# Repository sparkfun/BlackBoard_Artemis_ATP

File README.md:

**NOTE:** *This product has been retired from our catalog. There is an updated RedBoard version available: [DEV-15442]https://www.sparkfun.com/products/15442). If you are looking for more up-to-date info, please check out some of these resources to see how other users are still hacking and improving on this product version.*

* *[SparkFun Artemis Forum](https://forum.sparkfun.com/viewforum.php?f=167)*
* *[Comments Here on GitHub](https://github.com/sparkfun/BlackBoard_Artemis_ATP/issues)*

SparkFun BlackBoard Artemis ATP
============================

[*SparkFun BlackBoard Artemis ATP (SPX-15412)*](https://www.sparkfun.com/products/15412)

The BlackBoard Artemis ATP is affectionately called 'All the Pins!' at SparkFun. The Artemis module has 48 GPIO and this board breaks out absolutely every one of them in a familiar Mega like form factor. What's with the silkscreen labels? They're all over the place. We decided to label the pins as they are assigned on the Apollo3 IC itself. This makes finding the pin with the function you desire a lot easier. Have a look at the [full pin map](https://cdn.sparkfun.com/assets/8/2/3/3/c/Apollo3_Pad_Mapping.pdf) from the Apollo3 datasheet. If you really need to test out the 4-bit SPI functionality of the Artemis you're going to need to access pins 4, 22, 23, and 26. Need to try out the differential ADC port 1? Pins 14 and 15. The BlackBoard Artemis ATP will allow you to flex the impressive capabilities of the Artemis module.

The BlackBoard Artemis ATP has the improved power conditioning and USB to serial that we've refined over the years on our BlackBoard line of products. A modern USB-C connector make programming easy. A Qwiic connector makes I<sup>2</sup>C easy. The ATP is fully compatible with SparkFun's Arduino core and can be programmed easily under the Arduino IDE. We've exposed the JTAG connector for more advanced users who prefer to use the power and speed of professional tools. If you need a *lot* of a GPIO with a simple to program, ready to go to market module, the ATP is the fix you need. We've added a digital MEMS microphone for folks wanting to experiment with always-on voice commands with TensorFlow and machine learning. We've even added a convenient jumper to measure current consumption for low power testing.

With 1M flash and 384k RAM you'll have plenty of room for your sketches. The Artemis module runs at 48MHz with a 96MHz turbo mode available and with Bluetooth to boot!

The SparkFun BlackBoard Artemis ATP is a powerful platform if you're interesting in testing out the full capabilities of the SparkFun Artemis module. If you're looking for more compact solution, be sure to checkout our Nano and Uno footprints for more hacker friendly products.

**Note:** We are actively working on getting FCC and compliance certifications for the SparkFun Artemis Module. Once our certifications are complete we will be moving the ATP to a RedBoard format with the FCC Certified version of the Artemis on board. *Please be aware* that this could happen as soon as a few weeks to a month so this BlackBoard version is for those of you who can't wait and want to start using the SparkFun Artemis as soon as possible!

Repository Contents
-------------------
* **/Hardware** - Eagle design files (.brd, .sch)

Documentation
-------------------
* **[BlackBoard Artemis ATP Hookup Guide](https://learn.sparkfun.com/tutorials/hookup-guide-for-the-blackboard-artemis-atp)** - Hookup Guide for the BlackBoard Artemis ATP
* **[Designing with the SparkFun Artemis](https://learn.sparkfun.com/tutorials/designing-with-the-sparkfun-artemis)** - Layout and design considerations when using the Artemis module.
* **[Artemis Development with Arduino](https://learn.sparkfun.com/tutorials/artemis-development-with-arduino)** - Introduction to the Arduino core for the Artemis Module.
* **[Ambiq Apollo3 SDK SetUp](https://learn.sparkfun.com/tutorials/using-sparkfun-edge-board-with-ambiq-apollo3-sdk)** - Getting set up with the Apollo3 Software Development Kit.
* **[CH340E USB to serial IC Drivers](https://www.sparkfun.com/ch340)**

License Information
-------------------

This product is _**open source**_! 

Please review the LICENSE.md file for license information. 

If you have any questions or concerns on licensing, please contact techsupport@sparkfun.com.

Please use, reuse, and modify these files as you see fit. Please maintain attribution to SparkFun Electronics and release any derivative under the same license.

Distributed as-is; no warranty is given.

- Your friends at SparkFun.

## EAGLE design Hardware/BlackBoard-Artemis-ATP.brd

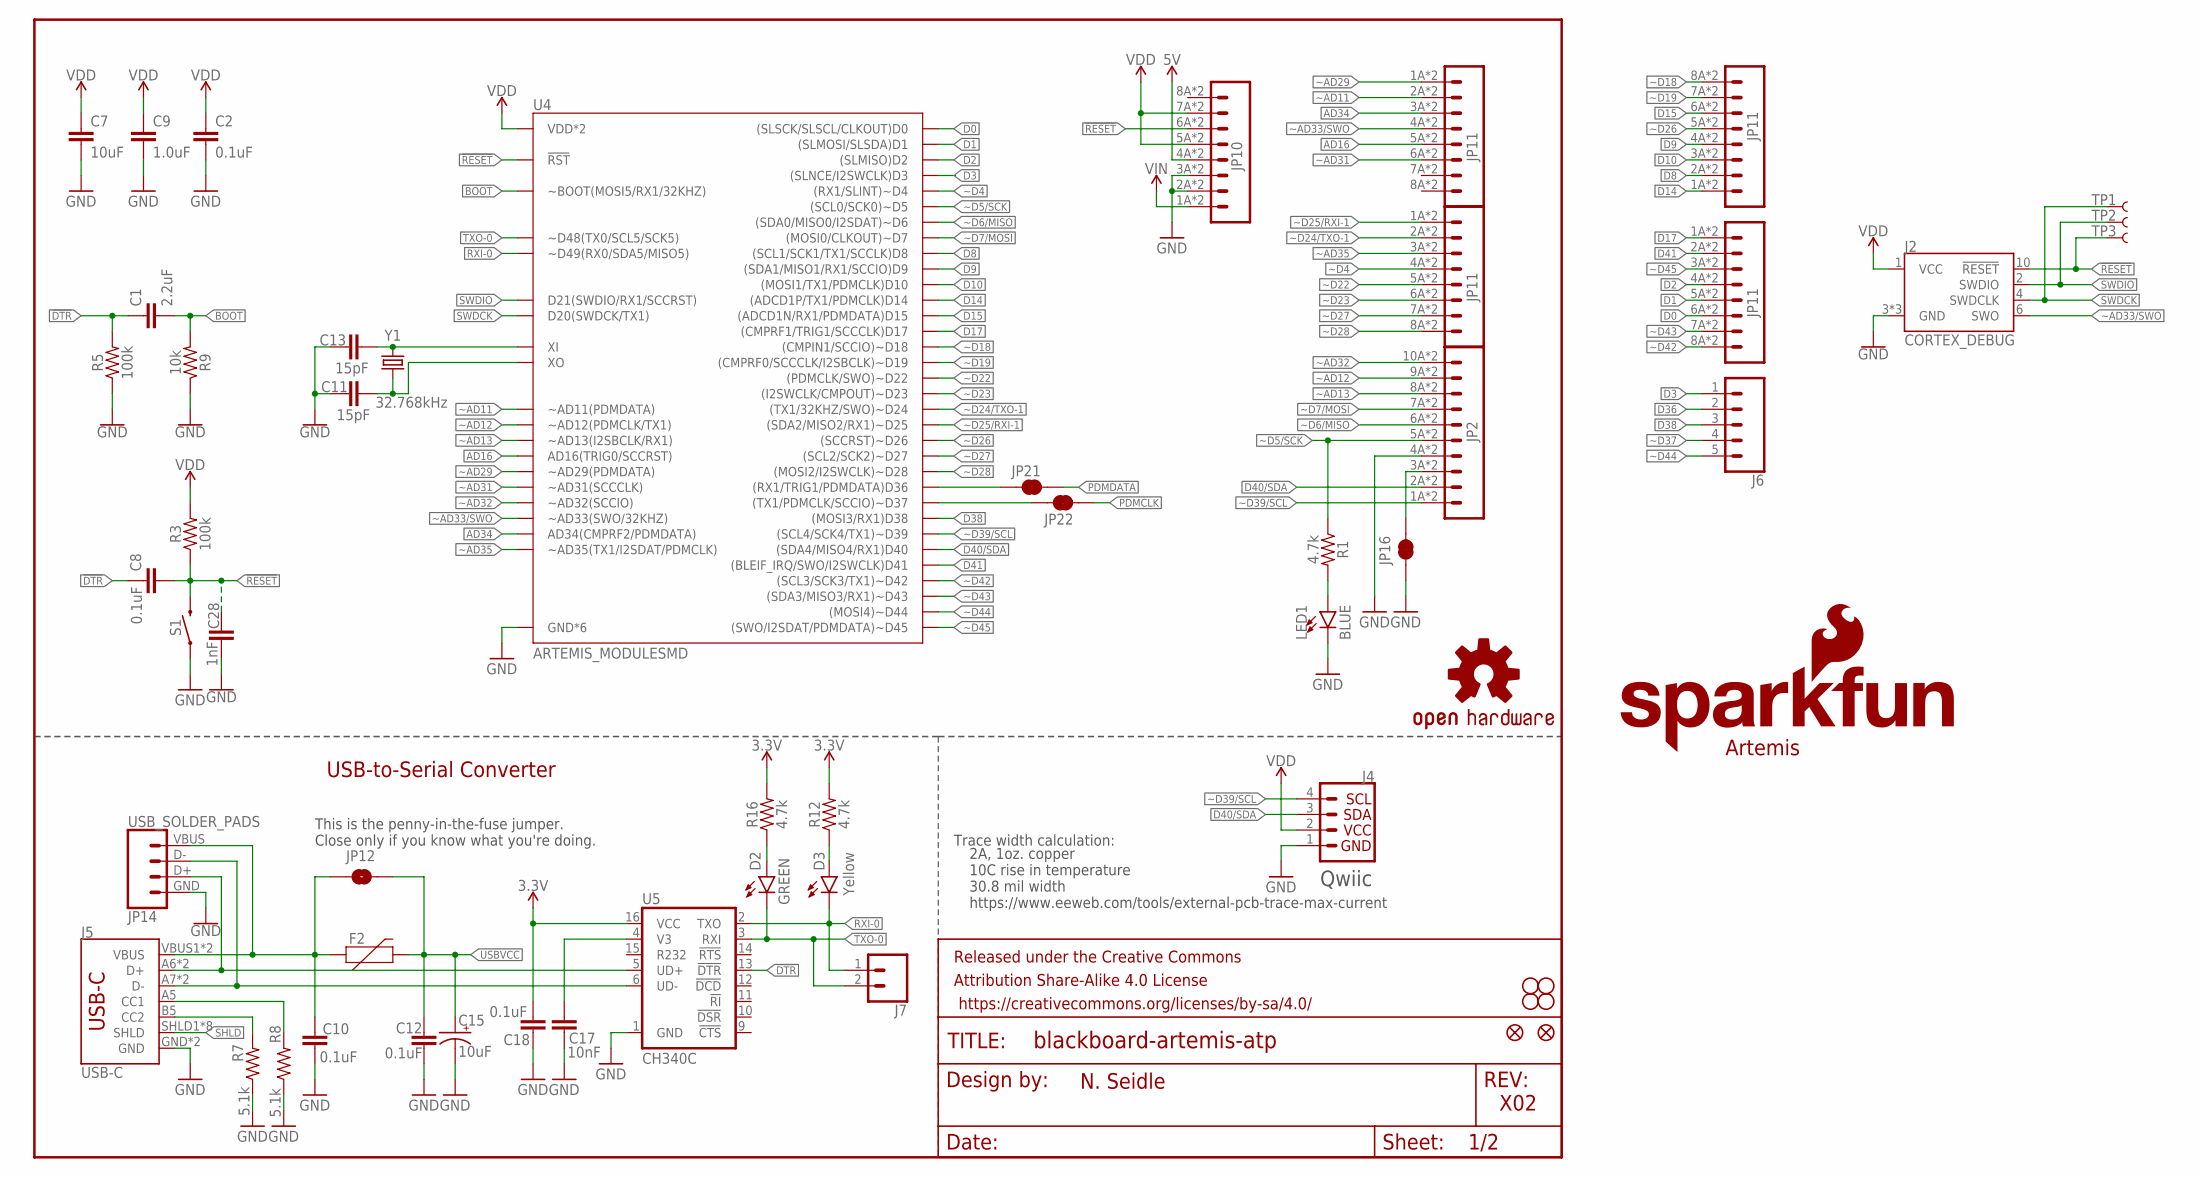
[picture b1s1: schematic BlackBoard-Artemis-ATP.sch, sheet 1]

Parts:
C1: 2.2uF; 0603
C2, C8, C10, C12, C18: 0.1uF; 0603
C7: 10uF; 0603
C9: 1.0uF; 0603
C11, C13: 15pF; 0603
C15: 10uF; EIA3216
C17: 10nF; 0603
C28: 1nF; 0603
D2: GREEN; LED-1206
D3: Yellow; LED-1206
F2: 6V/2A; 1210
FRAME1: FRAME-LETTER; CREATIVE_COMMONS
J2: CORTEX_DEBUG; 2X5-PTH-1.27MM-NO_SILK
J4: QWIIC_CONNECTORJS-1MM; JST04_1MM_RA
J5: USB-C; USB-C-16P
J6: CONN_05NO_SILK; 1X05_NO_SILK
J7: CONN_021X02_NO_SILK; 1X02_NO_SILK
JP1: SFE_LOGO_NAME.1_INCH; SFE_LOGO_NAME_.1
JP2: M10SMD_COMBO; 1X10_SMD_COMBINED
JP3, JP4, JP5, JP6: STAND-OFF
JP7: SFE_LOGO_FLAME.1_INCH; SFE_LOGO_FLAME_.1
JP8, JP9: FIDUCIAL1X2; FIDUCIAL-1X2
JP10: M08SMD-COMBO; 1X08_SMD_COMBINED
JP11, JP13, JP19, JP20: JP11; 1X08_SMD_COMBINED
JP12: JUMPER-SMT_2_NO_SILK; SMT-JUMPER_2_NO_SILK
JP14: USB_SOLDER_PADS; USB-SOLDER-PADS
JP16, JP21, JP22: JUMPER-SMT_2_NC_TRACE_SILK; SMT-JUMPER_2_NC_TRACE_SILK
LED1: BLUE; LED-1206
R1, R12, R16: 4.7k; 0603
R3, R5: 100k; 0603
R7, R8: 5.1k; 0603
R9: 10k; 0603
S1: MOMENTARY-SWITCH-SPST-SMD-5.2-TALL-REDUNDANT; TACTILE_SWITCH_SMD_5.2MM
TP1, TP2, TP3: TEST-POINT3X5; PAD.03X.05
U4: ARTEMIS_MODULESMD; ARTEMIS_FP
U5: CH340C; SO016
U$16: OSHW-LOGOS; OSHW-LOGO-S
Y1: 32.768kHz; CRYSTAL-SMD-3.2X1.5MM

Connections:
3.3V: C18.1, R12.2, R16.2, U5.16 (VCC); also elsewhere on the board
5V: JP10.4A (4), JP10.4B (4); also elsewhere on the board
!DTR: C1.1, C8.1, R5.2, U5.13 (!DTR)
!RESET: C8.2, C28.1, J2.10 (!RESET), JP10.6A (6), JP10.6B (6), R3.1, S1.3 (2), S1.4 (2), TP3.P$1, U4.~RST (!RST)
AD16: JP13.5A (5), JP13.5B (5), U4.AD16 (AD16(TRIG0/SCCRST))
AD34: JP13.3A (3), JP13.3B (3), U4.AD34 (AD34(CMPRF2/PDMDATA))
BOOT: C1.2, R9.2, U4.BOOT (~BOOT(MOSI5/RX1/32KHZ))
CC1: J5.A5 (CC1), R8.2
CC2: J5.B5 (CC2), R7.2
D0: JP20.6A (6), JP20.6B (6), U4.D0 ((SLSCK/SLSCL/CLKOUT)D0)
D1: JP20.5A (5), JP20.5B (5), U4.D1 ((SLMOSI/SLSDA)D1)
D2: JP20.4A (4), JP20.4B (4), U4.D2 ((SLMISO)D2)
D3: J6.1, U4.D3 ((SLNCE/I2SWCLK)D3)
D8: JP19.2A (2), JP19.2B (2), U4.D8 ((SCL1/SCK1/TX1/SCCLK)D8)
D9: JP19.4A (4), JP19.4B (4), U4.D9 ((SDA1/MISO1/RX1/SCCIO)D9)
D10: JP19.3A (3), JP19.3B (3), U4.D10 ((MOSI1/TX1/PDMCLK)D10)
D14: JP19.1A (1), JP19.1B (1), U4.D14 ((ADCD1P/TX1/PDMCLK)D14)
D15: JP19.6A (6), JP19.6B (6), U4.D15 ((ADCD1N/RX1/PDMDATA)D15)
D17: JP20.1A (1), JP20.1B (1), U4.D17 ((CMPRF1/TRIG1/SCCCLK)D17)
D36: J6.2, JP21.1, U4.D36 ((RX1/TRIG1/PDMDATA)D36)
D38: J6.3, U4.D38 ((MOSI3/RX1)D38)
D40/SDA: J4.3, JP2.2A (2), JP2.2B (2), U4.D40 ((SDA4/MISO4/RX1)D40)
D41: JP20.2A (2), JP20.2B (2), U4.D41 ((BLEIF_IRQ/SWO/I2SWCLK)D41)
D+: J5.A6 (D+), J5.B6 (D+), JP14.D+ (3), U5.5 (UD+)
D-: J5.A7 (D-), J5.B7 (D-), JP14.D- (2), U5.6 (UD-)
GND: C2.1, C7.2, C9.2, C10.2, C11.1, C12.2, C13.1, C15.-, C17.2, C18.2, C28.2, J2.3 (GND), J2.5 (GND), J2.9 (GND), J4.1, J5.GND, J5.GND2 (GND), JP2.4A (4), JP2.4B (4), JP10.2A (2), JP10.2B (2), JP10.3A (3), JP10.3B (3), JP14.GND (4), JP16.1, LED1.C, R5.1, R7.1, R8.1, R9.1, S1.1, S1.2 (1), U4.GND@1 (GND*6), U4.GND@22 (GND*6), U4.GND@38 (GND*6), U4.GND@39 (GND*6), U4.GND@47 (GND*6), U4.GND@59 (GND*6), U5.1 (GND); also elsewhere on the board
unnamed: LED1.A, R1.2
unnamed: D2.A, R16.1
unnamed: C17.1, U5.4 (V3)
unnamed: C11.2, U4.XO, Y1.P$2 (2)
unnamed: C13.2, U4.XI, Y1.P$1 (1)
unnamed: D3.A, R12.1
unnamed: JP2.3A (3), JP2.3B (3), JP16.2
PDMCLK: JP22.2; also elsewhere on the board
PDMDATA: JP21.2; also elsewhere on the board
RXI-0: D3.C, J7.1, U4.RXI-0 (~D49(RX0/SDA5/MISO5)), U5.2 (TXO)
SHLD: J5.SHLD1 (SHLD), J5.SHLD2 (SHLD), J5.SHLD3 (SHLD), J5.SHLD4 (SHLD), J5.SHLD5 (SHLD), J5.SHLD6 (SHLD), J5.SHLD7 (SHLD), J5.SHLD8 (SHLD)
SWDCK: J2.4 (SWDCLK), TP1.P$1, U4.SWDCK (D20(SWDCK/TX1))
SWDIO: J2.2 (SWDIO), TP2.P$1, U4.SWDIO (D21(SWDIO/RX1/SCCRST))
TXO-0: D2.C, J7.2, U4.TXO-0 (~D48(TX0/SCL5/SCK5)), U5.3 (RXI)
USBVCC: C12.1, C15.+, F2.2, JP12.2; also elsewhere on the board
VDD: C2.2, C7.1, C9.1, J2.1 (VCC), J4.2, JP10.5A (5), JP10.5B (5), JP10.7A (7), JP10.7B (7), R3.2, U4.VDD@36 (VDD*2), U4.VDD@37 (VDD*2); also elsewhere on the board
VIN: JP10.1A (1), JP10.1B (1); also elsewhere on the board
VUSB: C10.1, F2.1, J5.VBUS1 (VBUS), J5.VBUS2 (VBUS), JP12.1, JP14.VBUS (1); also elsewhere on the board
~AD11: JP13.2A (2), JP13.2B (2), U4.~AD11 (~AD11(PDMDATA))
~AD12: JP2.9A (9), JP2.9B (9), U4.~AD12 (~AD12(PDMCLK/TX1))
~AD13: JP2.8A (8), JP2.8B (8), U4.~AD13 (~AD13(I2SBCLK/RX1))
~AD29: JP13.1A (1), JP13.1B (1), U4.~AD29 (~AD29(PDMDATA))
~AD31: JP13.6A (6), JP13.6B (6), U4.~AD31 (~AD31(SCCCLK))
~AD32: JP2.10A (10), JP2.10B (10), U4.~AD32 (~AD32(SCCIO))
~AD33/SWO: J2.6 (SWO), JP13.4A (4), JP13.4B (4), U4.~AD33/SWO (~AD33(SWO/32KHZ))
~AD35: JP11.3A (3), JP11.3B (3), U4.~AD35 (~AD35(TX1/I2SDAT/PDMCLK))
~D4: JP11.4A (4), JP11.4B (4), U4.~D4 ((RX1/SLINT)~D4)
~D5/SCK: JP2.5A (5), JP2.5B (5), R1.1, U4.~D5 ((SCL0/SCK0)~D5)
~D6/MISO: JP2.6A (6), JP2.6B (6), U4.~D6 ((SDA0/MISO0/I2SDAT)~D6)
~D7/MOSI: JP2.7A (7), JP2.7B (7), U4.D7 ((MOSI0/CLKOUT)~D7)
~D18: JP19.8A (8), JP19.8B (8), U4.~D18 ((CMPIN1/SCCIO)~D18)
~D19: JP19.7A (7), JP19.7B (7), U4.~D19 ((CMPRF0/SCCCLK/I2SBCLK)~D19)
~D22: JP11.5A (5), JP11.5B (5), U4.~D22 ((PDMCLK/SWO)~D22)
~D23: JP11.6A (6), JP11.6B (6), U4.~D23 ((I2SWCLK/CMPOUT)~D23)
~D24/TXO-1: JP11.2A (2), JP11.2B (2), U4.~D24 ((TX1/32KHZ/SWO)~D24)
~D25/RXI-1: JP11.1A (1), JP11.1B (1), U4.~D25 ((SDA2/MISO2/RX1)~D25)
~D26: JP19.5A (5), JP19.5B (5), U4.~D26 ((SCCRST)~D26)
~D27: JP11.7A (7), JP11.7B (7), U4.~D27 ((SCL2/SCK2)~D27)
~D28: JP11.8A (8), JP11.8B (8), U4.~D28 ((MOSI2/I2SWCLK)~D28)
~D37: J6.4, JP22.1, U4.~D37 ((TX1/PDMCLK/SCCIO)~D37)
~D39/SCL: J4.4, JP2.1A (1), JP2.1B (1), U4.~D39 ((SCL4/SCK4/TX1)~D39)
~D42: JP20.8A (8), JP20.8B (8), U4.~D42 ((SCL3/SCK3/TX1)~D42)
~D43: JP20.7A (7), JP20.7B (7), U4.~D43 ((SDA3/MISO3/RX1)~D43)
~D44: J6.5, U4.~D44 ((MOSI4)~D44)
~D45: JP20.3A (3), JP20.3B (3), U4.~D45 ((SWO/I2SDAT/PDMDATA)~D45)

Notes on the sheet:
Artemis
USB-to-Serial Converter
N. Seidle
X02
Qwiic
This is the penny-in-the-fuse jumper. Close only if you know what you're doing.
Trace width calculation:
2A, 1oz. copper 10C rise in temperature 30.8 mil width https://www.eeweb.com/tools/external-pcb-trace-max-current

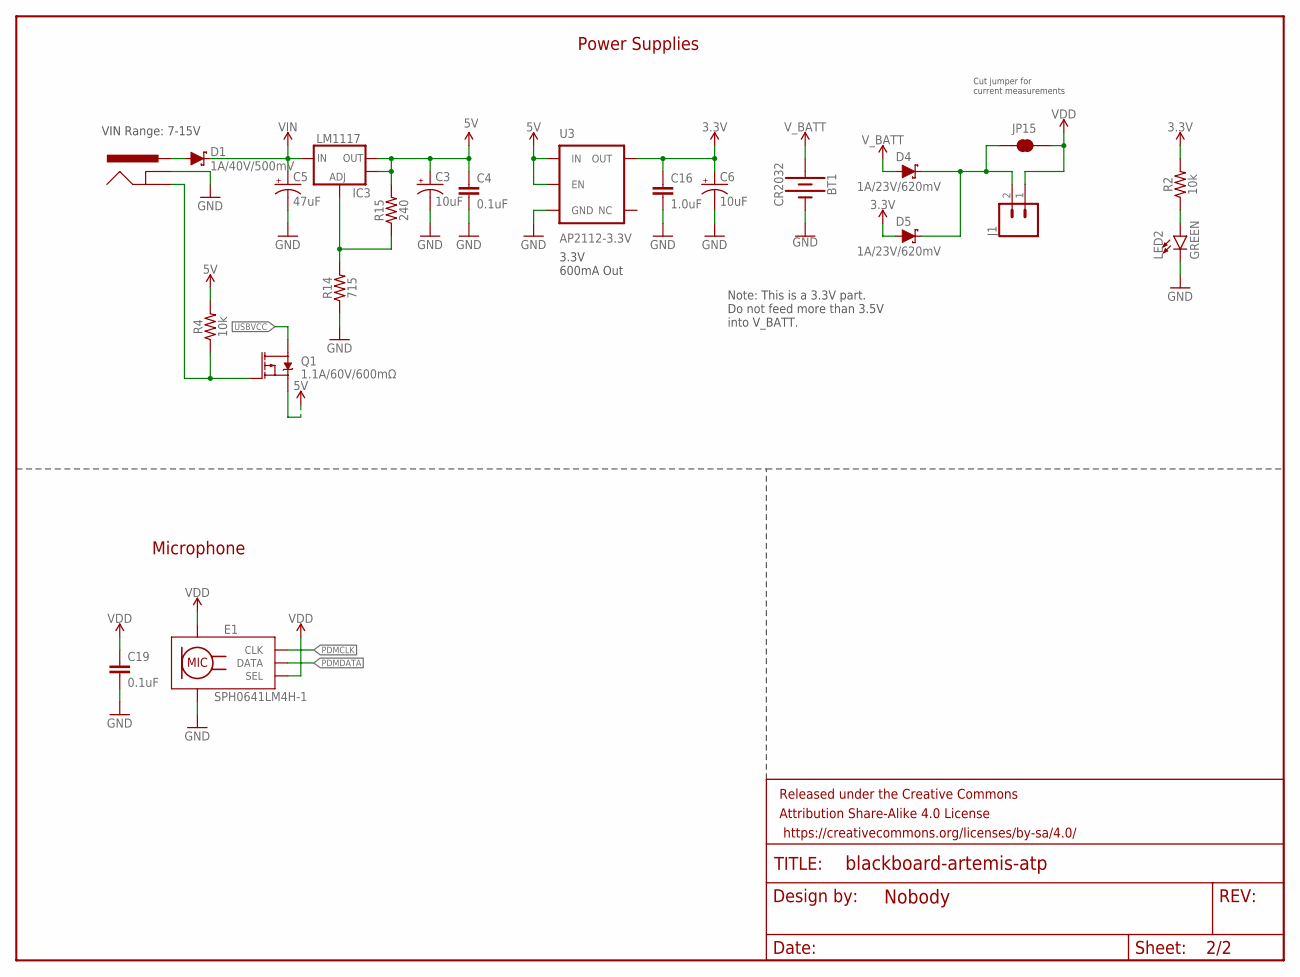
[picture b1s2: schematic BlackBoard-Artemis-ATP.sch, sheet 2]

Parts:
BT1: CR2032; BATTCON_20MM_4LEGS_OVERPASTE
C3, C6: 10uF; EIA3216
C4, C19: 0.1uF; 0603
C5: 47uF; PANASONIC_D
C16: 1.0uF; 0603
D1: 1A/40V/500mV; SMA-DIODE
D4, D5: 1A/23V/620mV; SOD-323
E1: SPH0641LM4H-1; SPH0641LM4H-1_MICROPHONE
FRAME2: FRAME-LETTERNO_PACKAGE; DUMMY
IC3: LM1117; SOT223-ALT1
J1: CONN_021X02_NO_SILK; 1X02_NO_SILK
J3: POWER_JACKTOE; POWER_JACK_SMD_OVERPASTE_TOE
JP15: JUMPER-SMT_2_NC_TRACE_SILK; SMT-JUMPER_2_NC_TRACE_SILK
LED2: GREEN; LED-1206
Q1: 1.1A/60V/600mΩ; SOT23-3
R2, R4: 10k; 0603
R14: 715; 0603
R15: 240; 0603
U3: AP2112-3.3V; SOT23-5

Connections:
3.3V: C6.+, C16.1, D5.A, R2.2, U3.5 (OUT); also elsewhere on the board
5V: C3.+, C4.1, IC3.2 (OUT), IC3.4 (OUT), Q1.2 (S), R4.2, R15.2, U3.1 (IN), U3.3 (EN); also elsewhere on the board
GND: BT1.2 (-), C3.-, C4.2, C5.-, C6.-, C16.2, C19.2, E1.3 (GND), E1.6 (GND), E1.7 (GND), E1.8 (GND), J3.GND (GNDBREAK), LED2.C, R14.1, U3.2 (GND); also elsewhere on the board
INSERT: J3.P$4 (GND), Q1.1 (G), R4.1
unnamed: LED2.A, R2.1
unnamed: D4.C, D5.C, J1.2, JP15.1
unnamed: IC3.1 (ADJ), R14.2, R15.1
PDMCLK: E1.4 (CLK); also elsewhere on the board
PDMDATA: E1.1 (DATA); also elsewhere on the board
PWRIN: D1.A, J3.VIN0 (PWR)
USBVCC: Q1.3 (D); also elsewhere on the board
VDD: C19.1, E1.2 (SEL), E1.5 (VDD), J1.1, JP15.2; also elsewhere on the board
VIN: C5.+, D1.C, IC3.3 (IN); also elsewhere on the board
V_BATT: BT1.1 (+), D4.A

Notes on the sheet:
VIN Range: 7-15V
3.3V 600mA Out
Cut jumper for current measurements
Power Supplies
Microphone
Note: This is a 3.3V part. Do not feed more than 3.5V into V_BATT.

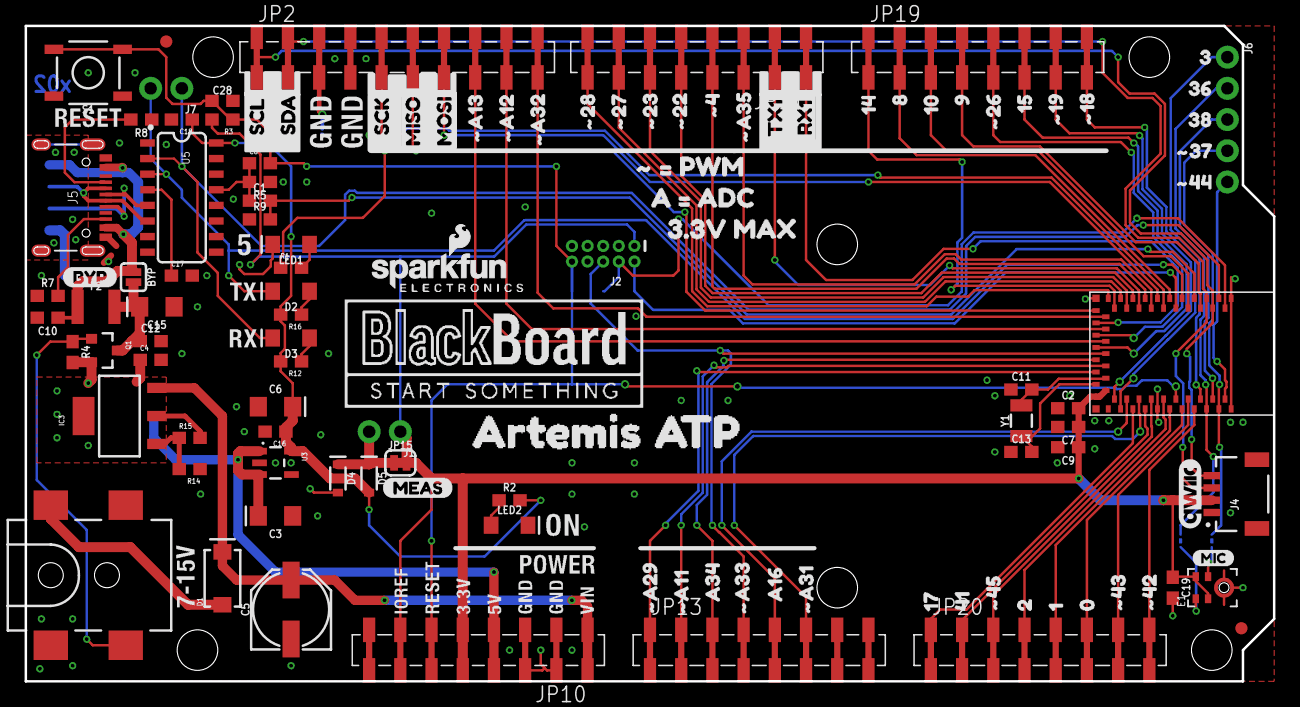
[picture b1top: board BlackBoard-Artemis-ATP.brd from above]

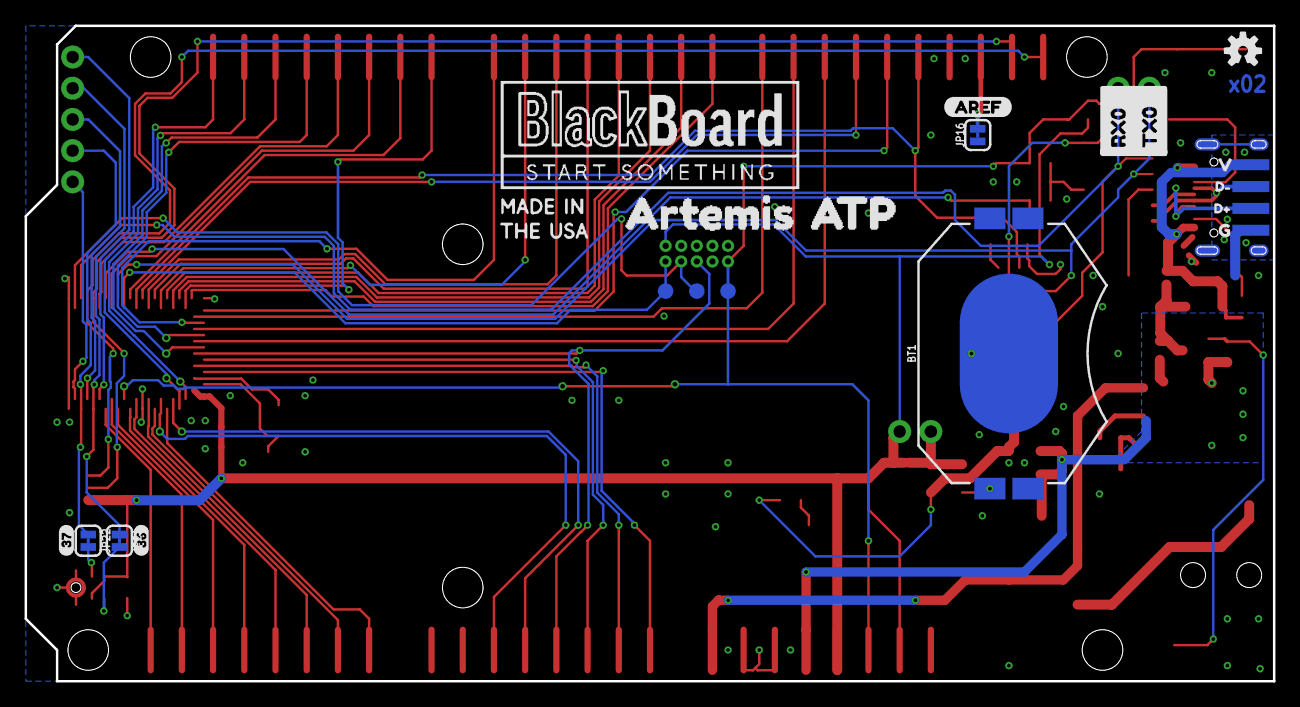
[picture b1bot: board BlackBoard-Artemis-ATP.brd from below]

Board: 2 copper layers, 101.6 x 53.3 mm, 149 parts (23 on the bottom side), 77 nets.

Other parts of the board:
BYP: BYP; SMT-JUMPER_2_NO_SILK
JP17, JP18: STAND-OFF
U$1, U$3: BLACKBOARDLOGO#PNG
U$2: D#3
U$4: MADEINUSA#PNG
U$9: QWIIC_COPYRIGHT_SMALL
U$10: D#4
U$11: G1
U$12: V0
U$13: #A332
U$14, U$15: ARTEMIS0
U$17: A160
U$18: SCL1
U$19: #48
U$20: AREF2
U$21: #229
U$22: SDA0
U$23: #3711
U$24: #187
U$25: #2310
U$26: #2711
U$27: #2812
U$28, U$61: ATP1
U$29: #A113
U$30: #A294
U$31: #A310
U$32: #196
U$33: #A357
U$34: #A1214
U$35: #A1315
U$36: #A3213
U$37: #264
U$38: A342
U$39: #4213
U$40: #4314
U$41: #4412
U$42: #4518
U$43: 015
U$44: 38
U$45: 81
U$46: 93
U$47: MISO8
U$48: MOSI7
U$49: RX01
U$50: SCK9
U$51: 102
U$52: 116
U$53: TX00
U$54: 140
U$55: 155
U$56: 217
U$57: 369
U$58: 1720
U$59: 3810
U$60: 4119
U$62: MIC0
U$63: 364
U$64: 373
U$66: #_#_PWM7
U$67: 3#3V_MAX2
U$68: BYP0
U$69: A_#_ADC6
U$70: MEAS3
U$71: RX11
U$72: TX10

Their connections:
USBVCC: BYP.2; also elsewhere on the board
VUSB: BYP.1; also elsewhere on the board

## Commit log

2019-05-22 Fixes from design review. Route away from antenna.
2019-05-22 Add panel files
2019-05-24 Moved SWDIO test point. Removed TP5/6.
2019-05-29 Move TP for easier testing. Remove TP on serial. Adjust sch blocks.
2019-06-20 Add ignore. Add panel files.

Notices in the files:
parts and their libraries:
SparkFun-Aesthetics: Licensing: CC v3.0 Share-Alike You are welcome to use this library for commercial purposes.
SparkFun-Aesthetics: Released under the Creative Commons Attribution Share-Alike 4.0 License
SparkFun-Aesthetics: https://creativecommons.org/licenses/by-sa/4.0
